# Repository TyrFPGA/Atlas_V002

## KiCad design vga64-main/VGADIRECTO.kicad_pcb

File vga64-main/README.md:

# vga64
Adaptador directo de hdmi a vga para la atlasfpga. Diseño usando Kicad 6.0

La profundidad actual que conseguimos de 64 colores usando 2 bits por color, por eso la llamamos vga64 aunque también podría llamarse vga222.

El adaptador puede ser usado solo o con una adaptador vga<->scart si el core lo permite sin problemas.

# Esquemas
[https://github.com/AtlasFPGA/vga64/blob/main/VGADIRECTO.pdf]

# Material
* 1 x PCB vga
* 1 x conector HDMI 
* 1 x conector VGA
* 1 x resistencia 1206 -  1k ohm
* 3 x resistencia 1206 - 820 ohm 
* 3 x resistencia 1206 - 240 ohm

# URL compras
* 1 x PCB lo hicimos en la página https://jlcpcb.com/ usando los gerbers: https://github.com/AtlasFPGA/vga64/raw/main/gerbers_vga64_atlas_1206.zip
* 1 x HDMI modelo 10029449-111RLF -> https://es.farnell.com/amphenol-icc-fci/10029449-111rlf/conector-hdmi-19-pos-hembra-smt/dp/2751197
* 1 x Conector VGA -> https://es.rs-online.com/web/p/conectores-d-sub/6740971
* 1 x resistencia 1206 -  1k ohm -> https://es.farnell.com/multicomp-pro/mp003719/res-1k-1-0-25w-1206-pel-c-gruesa/dp/3392916
* 3 x resistencia 1206 - 820 ohm -> https://es.farnell.com/multicomp-pro/mp003717/res-820r-1-0-25w-1206-pel-c-gruesa/dp/3392914
* 3 x resistencia 1206 - 240 ohm -> https://es.farnell.com/multicomp-pro/mp003703/res-240r-1-0-25w-1206-pel-c-gruesa/dp/3392898

# Equivalencias de pineado para cambiar en Quartus
```
## HDMI Direct ATLAS_V002_CYC1000                                         ### VGA222 adaptador de 64Colores
set_location_assignment PIN_L16 -to TMDS[0] # CLK-                        ### HS
set_location_assignment PIN_L15 -to TMDS[1] # CLK+ # clock channel        ### VS
set_location_assignment PIN_P1 -to TMDS[2]  # 0-                          ### BLUE[0]
set_location_assignment PIN_P2 -to TMDS[3]  # 0+   # blue channel         ### BLUE[1]
set_location_assignment PIN_J1 -to TMDS[4]  # 1-                          ### GREEN[0]
set_location_assignment PIN_J2 -to TMDS[5]  # 1+   # green channel        ### GREEN[1]
set_location_assignment PIN_N1 -to TMDS[6]  # 2-                          ### RED[0]
set_location_assignment PIN_N2 -to TMDS[7]  # 2+   # red channel          ### RED[1]
```

Proyecto original de @subcriticalia y @Nabateo.

Gracias a @Rhoderik por el convertir el proyecto a smd 1206 y a @Somhi (@somhic) por la ayuda / revisión como siempre.

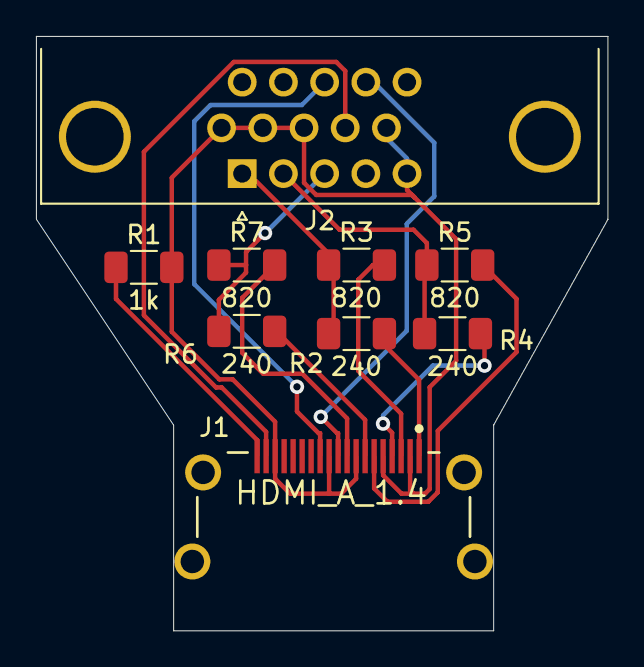
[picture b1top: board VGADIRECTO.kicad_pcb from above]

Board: 2 copper layers, 31.8 x 33.0 mm, 9 parts (0 on the bottom side), 14 nets.

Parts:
J1: HDMI_A_1.4; Amphenol_ICC-10029449-111RLF-MFG
J2: DB15_Female_HighDensity; DSUB-15-HD_Female_Horizontal_P2.29x2.54mm_EdgePinOffset3.03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
R1: 1k; R_1206_3216Metric_Pad1.30x1.75mm_HandSolder
R2, R4, R6: 240; R_1206_3216Metric_Pad1.30x1.75mm_HandSolder
R3, R5, R7: 820; R_1206_3216Metric_Pad1.30x1.75mm_HandSolder

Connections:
+5V: J1.18 (+5V), J2.9
GND: J1.2 (D2S), J1.5 (D1S), J1.8 (D0S), J1.11 (CKS), J1.17 (GND), J2.5, J2.6, J2.7, J2.8, J2.10, R1.2
unnamed: J1.19 (HPD/HEAC-), R1.1
VGA222_B0: J1.9 (D0-), R7.2
VGA222_B1: J1.7 (D0+), R6.2
VGA222_G0: J1.6 (D1-), R5.2
VGA222_G1: J1.4 (D1+), R4.2
VGA222_HS: J1.12 (CK-), J2.13
VGA222_R0: J1.3 (D2-), R3.2
VGA222_R1: J1.1 (D2+), R2.2
VGA222_VS: J1.10 (CK+), J2.14
VGAB: J2.3, R6.1, R7.1
VGAG: J2.2, R4.1, R5.1
VGAR: J2.1, R2.1, R3.1

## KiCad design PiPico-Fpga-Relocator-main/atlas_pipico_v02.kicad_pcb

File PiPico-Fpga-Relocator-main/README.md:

# PiPico-Fpga-Relocator
PCB for plug a PiPico on MKR bus for use Atlas resources

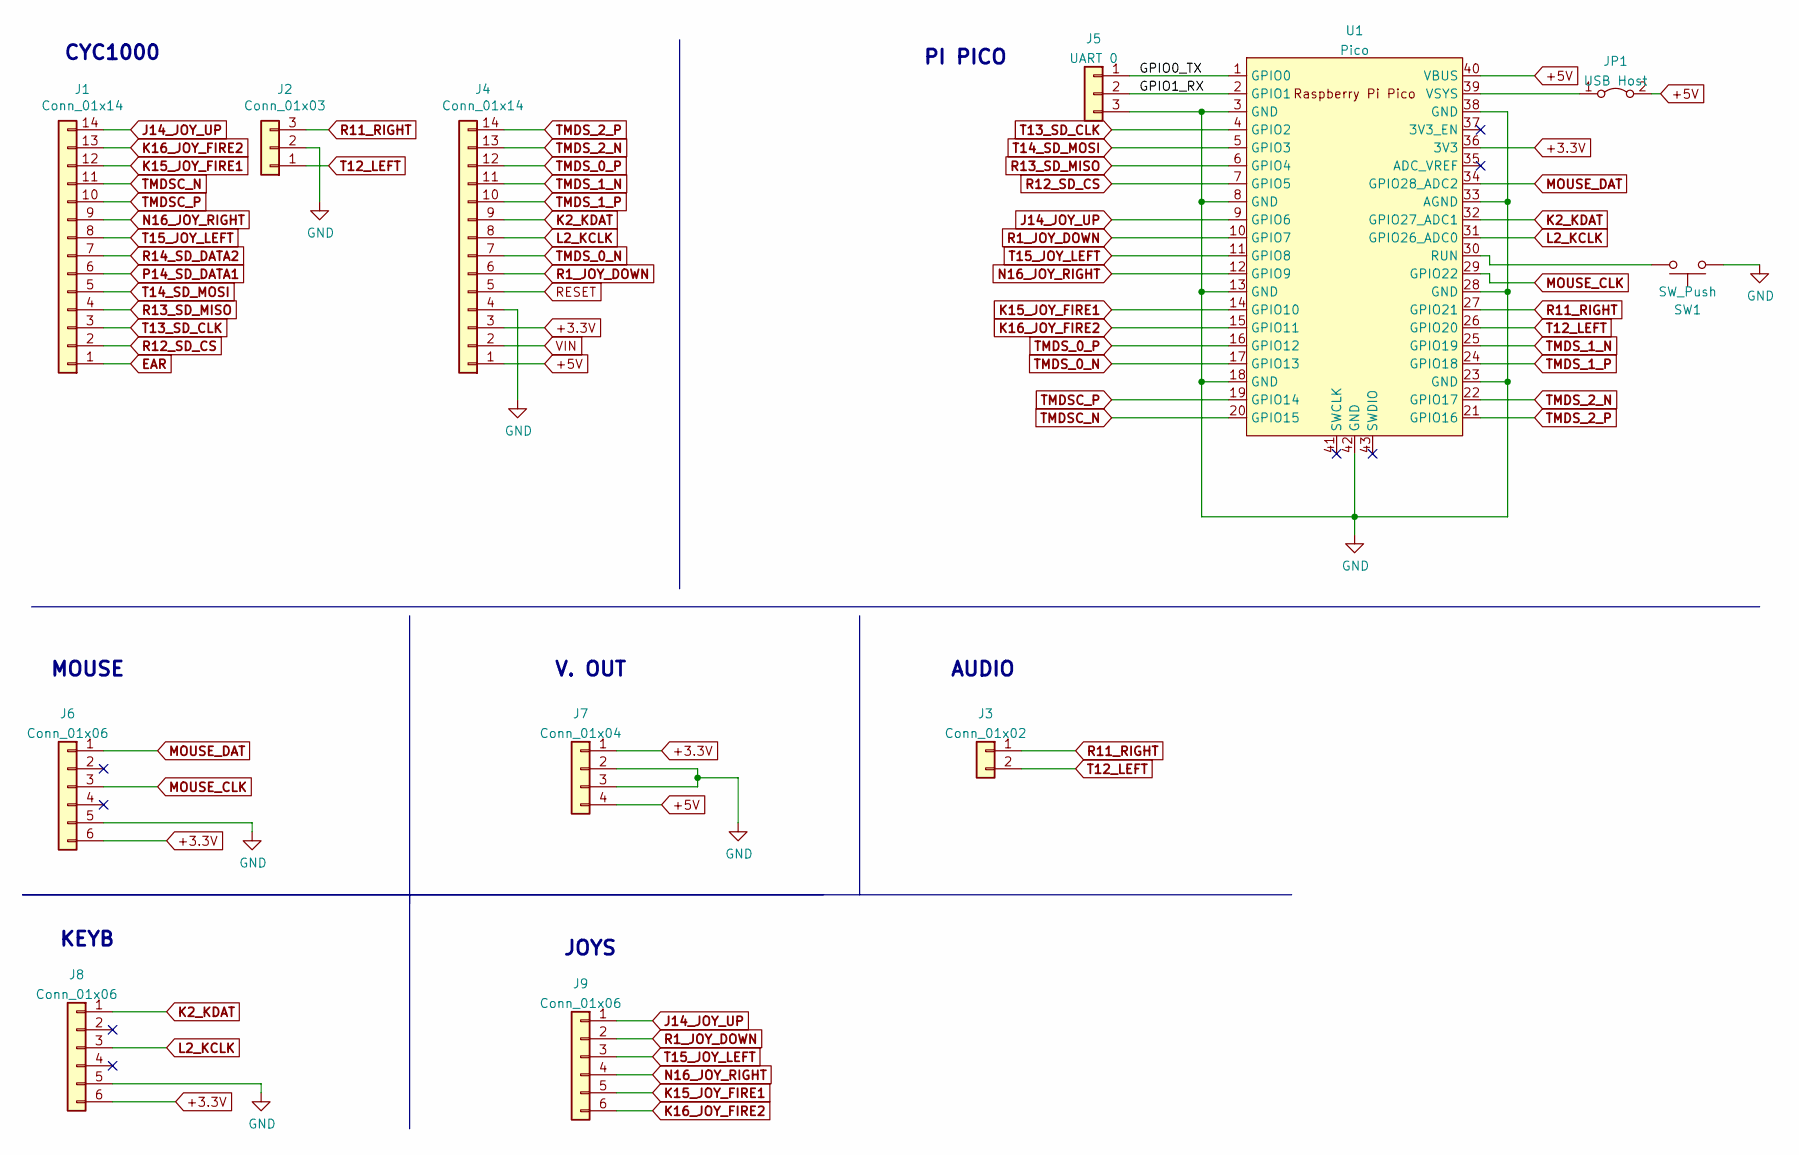
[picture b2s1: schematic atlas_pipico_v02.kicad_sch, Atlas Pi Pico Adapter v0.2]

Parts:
J1, J4: Conn_01x14; PinHeader_1x14_P2.54mm_Vertical
J2: Conn_01x03; PinHeader_1x03_P2.54mm_Vertical
J3: Conn_01x02; PinHeader_1x02_P2.54mm_Vertical
J5: UART 0; PinHeader_1x03_P2.54mm_Vertical
J6, J8, J9: Conn_01x06; PinHeader_1x06_P2.54mm_Vertical
J7: Conn_01x04; PinHeader_1x04_P2.54mm_Vertical
JP1: USB Host; PinHeader_1x02_P2.54mm_Vertical
SW1: SW_Push; SW_PUSH_6mm
U1: Pico; RPi_Pico_SMD_TH

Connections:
+3.3V: J4.3, J6.6, J7.1, J8.6, U1.36 (3V3)
+5V: J4.1, J7.4, JP1.2 (B), U1.40 (VBUS)
/GPIO0_TX: J5.1, U1.1 (GPIO0)
/GPIO1_RX: J5.2, U1.2 (GPIO1)
EAR: J1.1
GND: J2.2, J4.4, J5.3, J6.5, J7.2, J7.3, J8.5, SW1.2, U1.3 (GND), U1.8 (GND), U1.13 (GND), U1.18 (GND), U1.23 (GND), U1.28 (GND), U1.33 (AGND), U1.38 (GND), U1.42 (GND)
J14_JOY_UP: J1.14, J9.1, U1.9 (GPIO6)
K2_KDAT: J4.9, J8.1, U1.32 (GPIO27_ADC1)
K15_JOY_FIRE1: J1.12, J9.5, U1.14 (GPIO10)
K16_JOY_FIRE2: J1.13, J9.6, U1.15 (GPIO11)
L2_KCLK: J4.8, J8.3, U1.31 (GPIO26_ADC0)
MOUSE_CLK: J6.3, U1.29 (GPIO22)
MOUSE_DAT: J6.1, U1.34 (GPIO28_ADC2)
N16_JOY_RIGHT: J1.9, J9.4, U1.12 (GPIO9)
unnamed: JP1.1 (A), U1.39 (VSYS)
unnamed: SW1.1, U1.30 (RUN)
P14_SD_DATA1: J1.6
R1_JOY_DOWN: J4.6, J9.2, U1.10 (GPIO7)
R11_RIGHT: J2.3, J3.1, U1.27 (GPIO21)
R12_SD_CS: J1.2, U1.7 (GPIO5)
R13_SD_MISO: J1.4, U1.6 (GPIO4)
R14_SD_DATA2: J1.7
RESET: J4.5
T12_LEFT: J2.1, J3.2, U1.26 (GPIO20)
T13_SD_CLK: J1.3, U1.4 (GPIO2)
T14_SD_MOSI: J1.5, U1.5 (GPIO3)
T15_JOY_LEFT: J1.8, J9.3, U1.11 (GPIO8)
TMDSC_N: J1.11, U1.20 (GPIO15)
TMDSC_P: J1.10, U1.19 (GPIO14)
TMDS_0_N: J4.7, U1.17 (GPIO13)
TMDS_0_P: J4.12, U1.16 (GPIO12)
TMDS_1_N: J4.11, U1.25 (GPIO19)
TMDS_1_P: J4.10, U1.24 (GPIO18)
TMDS_2_N: J4.13, U1.22 (GPIO17)
TMDS_2_P: J4.14, U1.21 (GPIO16)
VIN: J4.2

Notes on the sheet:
MOUSE
CYC1000
AUDIO
KEYB
JOYS
PI PICO
V. OUT

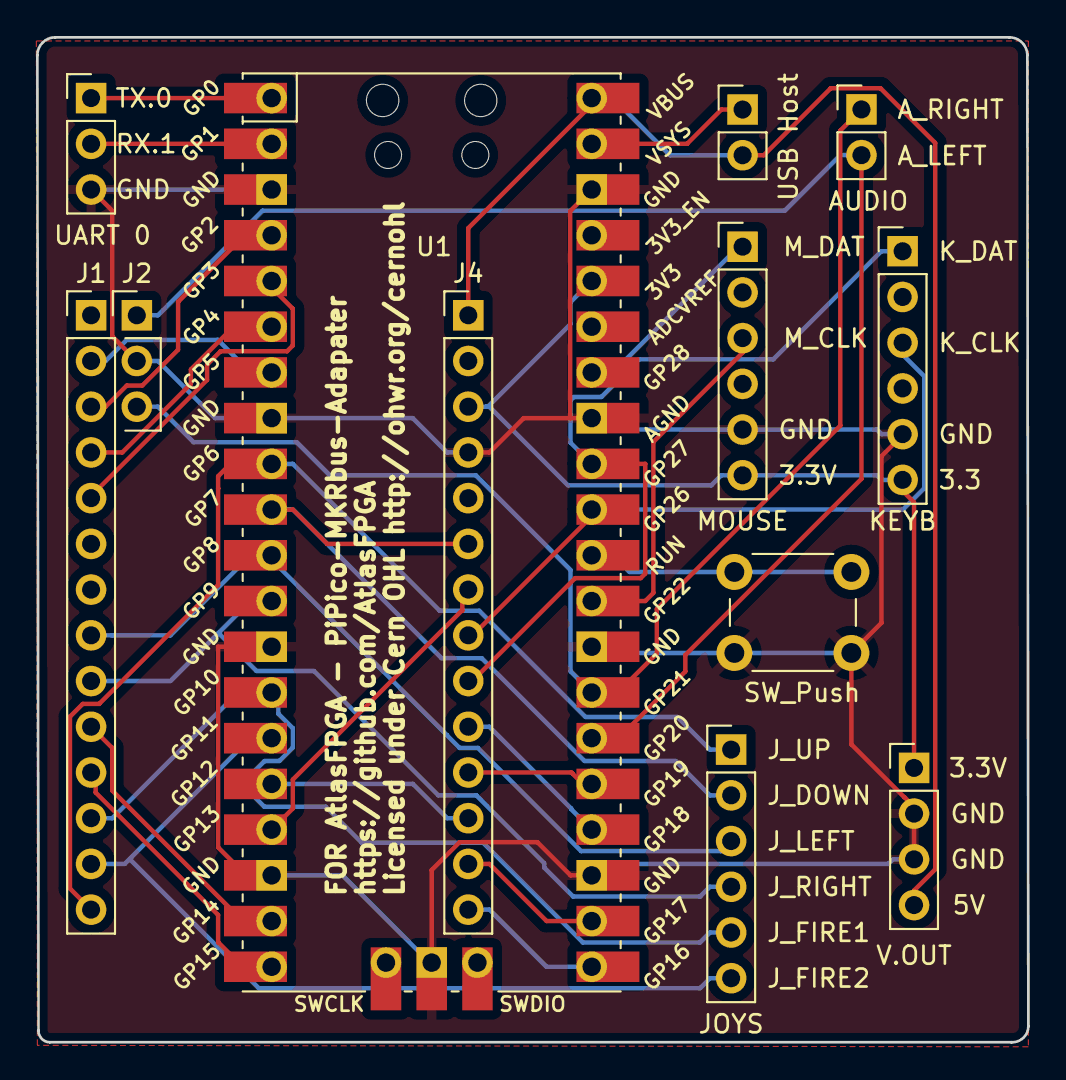
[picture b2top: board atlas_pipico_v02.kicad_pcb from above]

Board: 2 copper layers, 55.1 x 55.8 mm, 12 parts (0 on the bottom side), 31 nets.

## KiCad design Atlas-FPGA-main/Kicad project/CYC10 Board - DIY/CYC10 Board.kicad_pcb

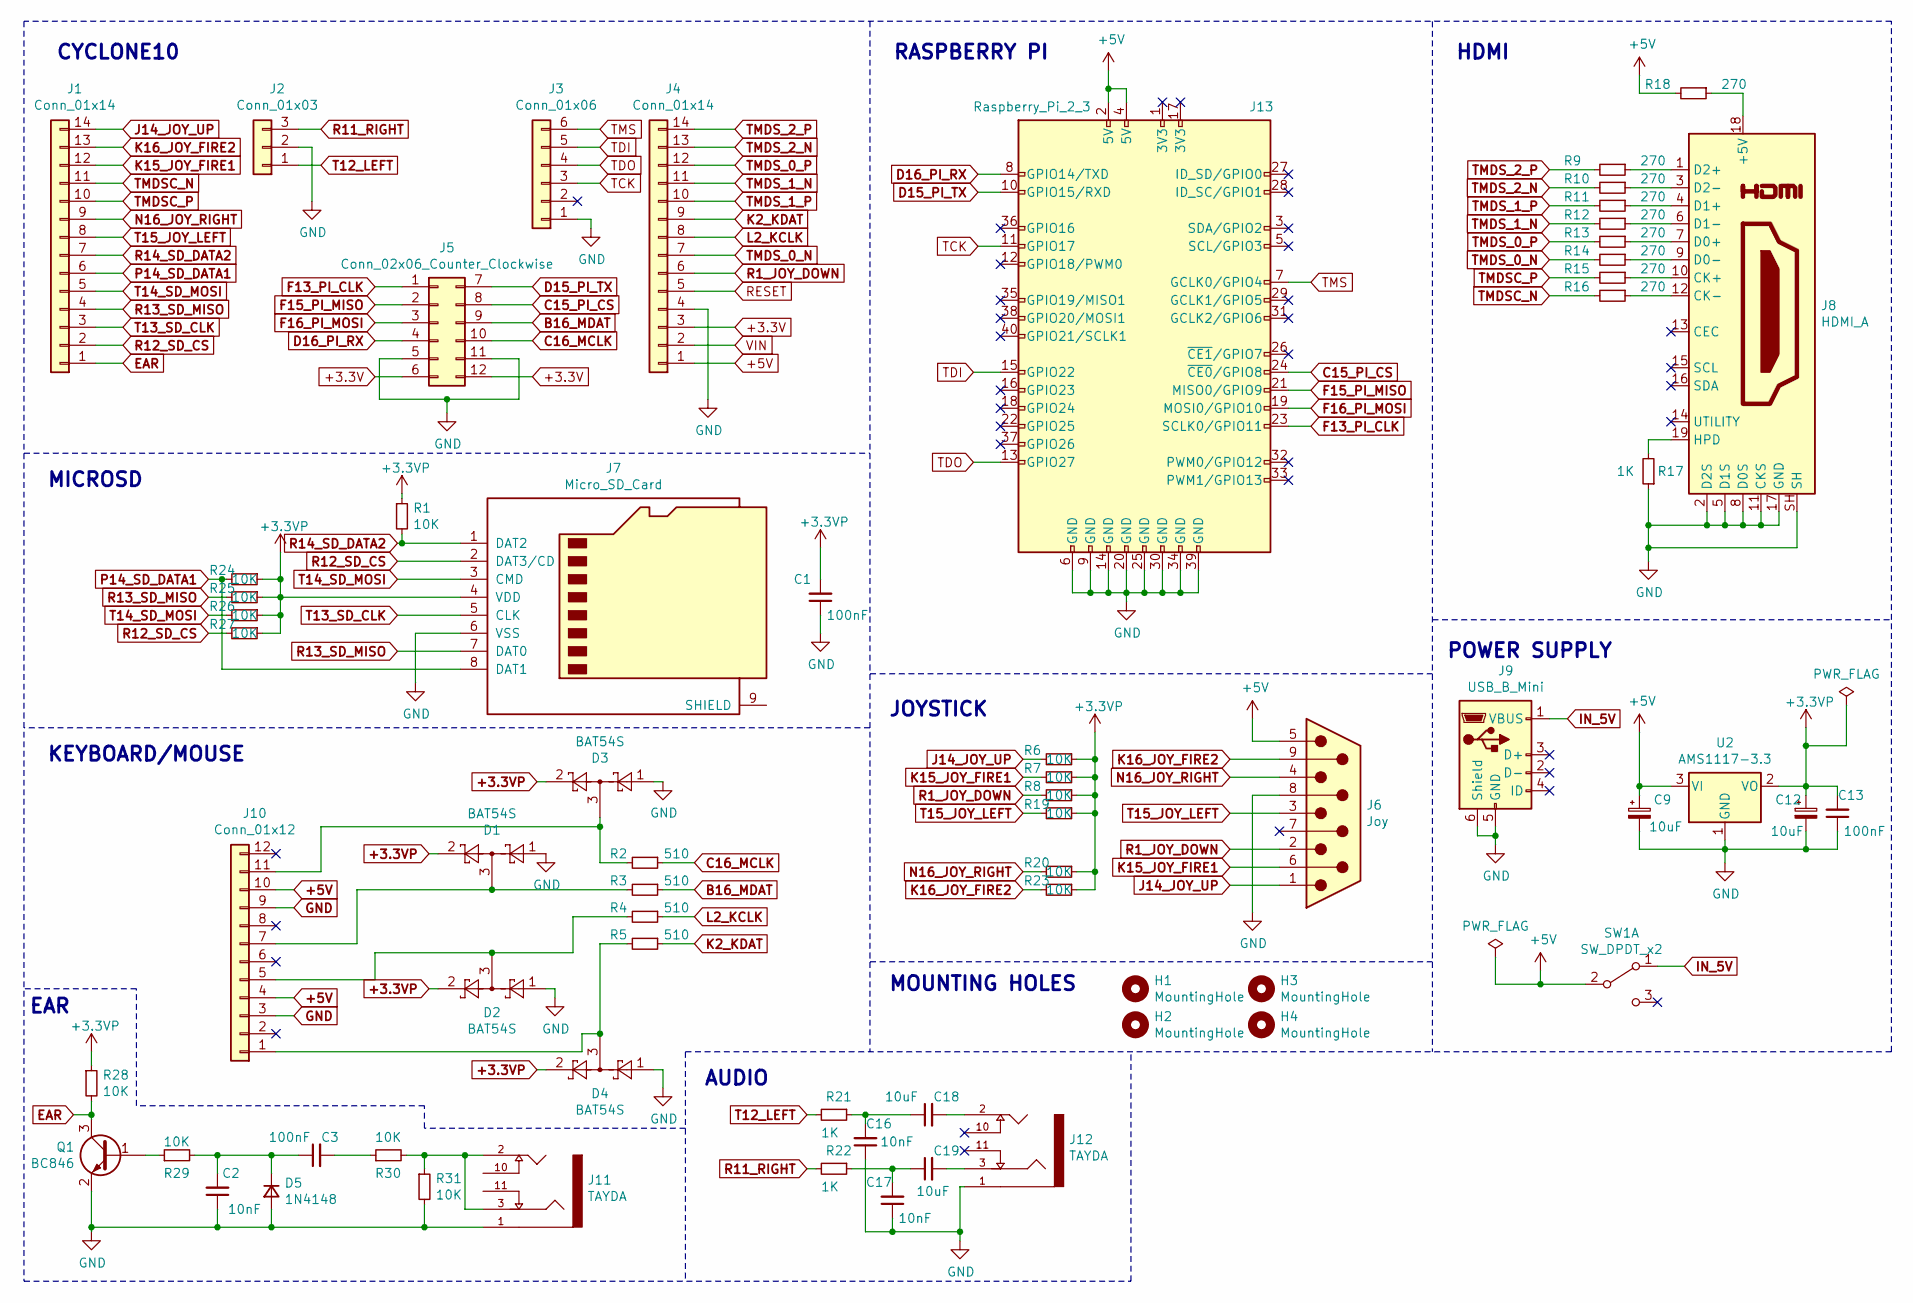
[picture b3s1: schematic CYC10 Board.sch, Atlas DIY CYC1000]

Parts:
C1, C3, C13: 100nF; C_0805_2012Metric
C2, C16, C17: 10nF; C_0805_2012Metric
C9, C12, C18, C19: 10uF; C_0805_2012Metric
D1, D2, D3, D4: BAT54S; SOT-23
D5: 1N4148; D_MiniMELF
H1, H2, H3, H4: MountingHole; MountingHole_3.2mm_M3
J1, J4: Conn_01x14; PinHeader_1x14_P2.54mm_Vertical
J2: Conn_01x03; PinHeader_1x03_P2.54mm_Vertical
J3: Conn_01x06; PinHeader_1x06_P2.54mm_Vertical
J5: Conn_02x06_Counter_Clockwise; PMOD
J6: Joy; DSUB-9_Male_Horizontal_P2.77x2.84mm_EdgePinOffset9.90mm_Hou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
J7: Micro_SD_Card; Conn_uSDcard1
J8: HDMI_A; HDMI_BIEN
J9: USB_B_Mini; USB_Mini-B_Wuerth_65100516121_Horizontal
J10: Conn_01x12; PS2_DOBLE
J11, J12: TAYDA; Tayda_Audio_Bien
J13: Raspberry_Pi_2_3; Conector_PI
Q1: BC846; SOT-23
R1, R6, R7, R8, R19, R20, R23, R24, R25, R26, R27, R28, R29, R30, R31: 10K; R_0805_2012Metric
R2, R3, R4, R5: 510; R_0805_2012Metric
R9, R10, R11, R12, R13, R14, R15, R16, R18: 270; R_0805_2012Metric
R17, R21, R22: 1K; R_0805_2012Metric
SW1: SW_DPDT_x2; Switch
U2: AMS1117-3.3; SOT-223-3_TabPin2

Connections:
+3.3V: J4.3, J5.6, J5.12
+3.3VP: C1.2, C12.1, C13.2, D1.2, D2.2, D3.2, D4.2, J7.4 (VDD), R1.1, R6.1, R7.1, R8.1, R19.1, R20.1, R23.1, R24.1, R25.1, R26.1, R27.1, R28.1, U2.2 (VO)
+5V: C9.1, J4.1, J6.5, J10.4, J10.10, J13.2 (5V), J13.4 (5V), R18.2, SW1.2 (B), U2.3 (VI)
B16_MDAT: J5.9, R3.1
C15_PI_CS: J5.8, J13.24 (~CE0~/GPIO8)
C16_MCLK: J5.10, R2.1
D15_PI_TX: J5.7, J13.10 (GPIO15/RXD)
D16_PI_RX: J5.4, J13.8 (GPIO14/TXD)
EAR: J1.1, Q1.3 (C), R28.2
F13_PI_CLK: J5.1, J13.23 (SCLK0/GPIO11)
F15_PI_MISO: J5.2, J13.21 (MISO0/GPIO9)
F16_PI_MOSI: J5.3, J13.19 (MOSI0/GPIO10)
GND: C1.1, C2.1, C9.2, C12.2, C13.1, C16.1, C17.1, D1.1, D2.1, D3.1, D4.1, D5.2 (A), J2.2, J3.1, J4.4, J5.5, J5.11, J6.8, J7.6 (VSS), J8.2 (D2S), J8.5 (D1S), J8.8 (D0S), J8.11 (CKS), J8.17 (GND), J8.SH, J9.5 (GND), J9.6 (Shield), J10.3, J10.9, J11.1, J12.1, J13.6 (GND), J13.9 (GND), J13.14 (GND), J13.20 (GND), J13.25 (GND), J13.30 (GND), J13.34 (GND), J13.39 (GND), Q1.2 (E), R17.1, R31.2, U2.1 (GND)
IN_5V: J9.1 (VBUS), SW1.1 (A)
J14_JOY_UP: J1.14, J6.1, R6.2
K2_KDAT: J4.9, R5.1
K15_JOY_FIRE1: J1.12, J6.6, R7.2
K16_JOY_FIRE2: J1.13, J6.9, R23.2
L2_KCLK: J4.8, R4.1
N16_JOY_RIGHT: J1.9, J6.4, R20.2
unnamed: C2.2, C3.1, D5.1 (K), R29.2
unnamed: C3.2, R30.1
unnamed: C16.2, C18.1, R21.1
unnamed: C17.2, C19.1, R22.1
unnamed: C18.2, J12.2
unnamed: C19.2, J12.3
unnamed: D1.3, J10.7, R3.2
unnamed: D2.3, J10.5, R4.2
unnamed: D3.3, J10.11, R2.2
unnamed: D4.3, J10.1, R5.2
unnamed: J8.1 (D2+), R9.1
unnamed: J8.3 (D2-), R10.1
unnamed: J8.4 (D1+), R11.1
unnamed: J8.6 (D1-), R12.1
unnamed: J8.7 (D0+), R13.1
unnamed: J8.9 (D0-), R14.1
unnamed: J8.10 (CK+), R15.1
unnamed: J8.12 (CK-), R16.1
unnamed: J8.18 (+5V), R18.1
unnamed: J8.19 (HPD), R17.2
unnamed: J11.2, J11.3, R30.2, R31.1
unnamed: Q1.1 (B), R29.1
P14_SD_DATA1: J1.6, J7.8 (DAT1), R24.2
R1_JOY_DOWN: J4.6, J6.2, R8.2
R11_RIGHT: J2.3, R22.2
R12_SD_CS: J1.2, J7.2 (DAT3/CD), R27.2
R13_SD_MISO: J1.4, J7.7 (DAT0), R25.2
R14_SD_DATA2: J1.7, J7.1 (DAT2), R1.2
RESET: J4.5
T12_LEFT: J2.1, R21.2
T13_SD_CLK: J1.3, J7.5 (CLK)
T14_SD_MOSI: J1.5, J7.3 (CMD), R26.2
T15_JOY_LEFT: J1.8, J6.3, R19.2
TCK: J3.3, J13.11 (GPIO17)
TDI: J3.5, J13.15 (GPIO22)
TDO: J3.4, J13.13 (GPIO27)
TMDSC_N: J1.11, R16.2
TMDSC_P: J1.10, R15.2
TMDS_0_N: J4.7, R14.2
TMDS_0_P: J4.12, R13.2
TMDS_1_N: J4.11, R12.2
TMDS_1_P: J4.10, R11.2
TMDS_2_N: J4.13, R10.2
TMDS_2_P: J4.14, R9.2
TMS: J3.6, J13.7 (GCLK0/GPIO4)
VIN: J4.2

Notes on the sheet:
JOYSTICK
POWER SUPPLY
AUDIO
KEYBOARD/MOUSE
MICROSD
CYCLONE10
RASPBERRY PI
HDMI
MOUNTING HOLES
EAR

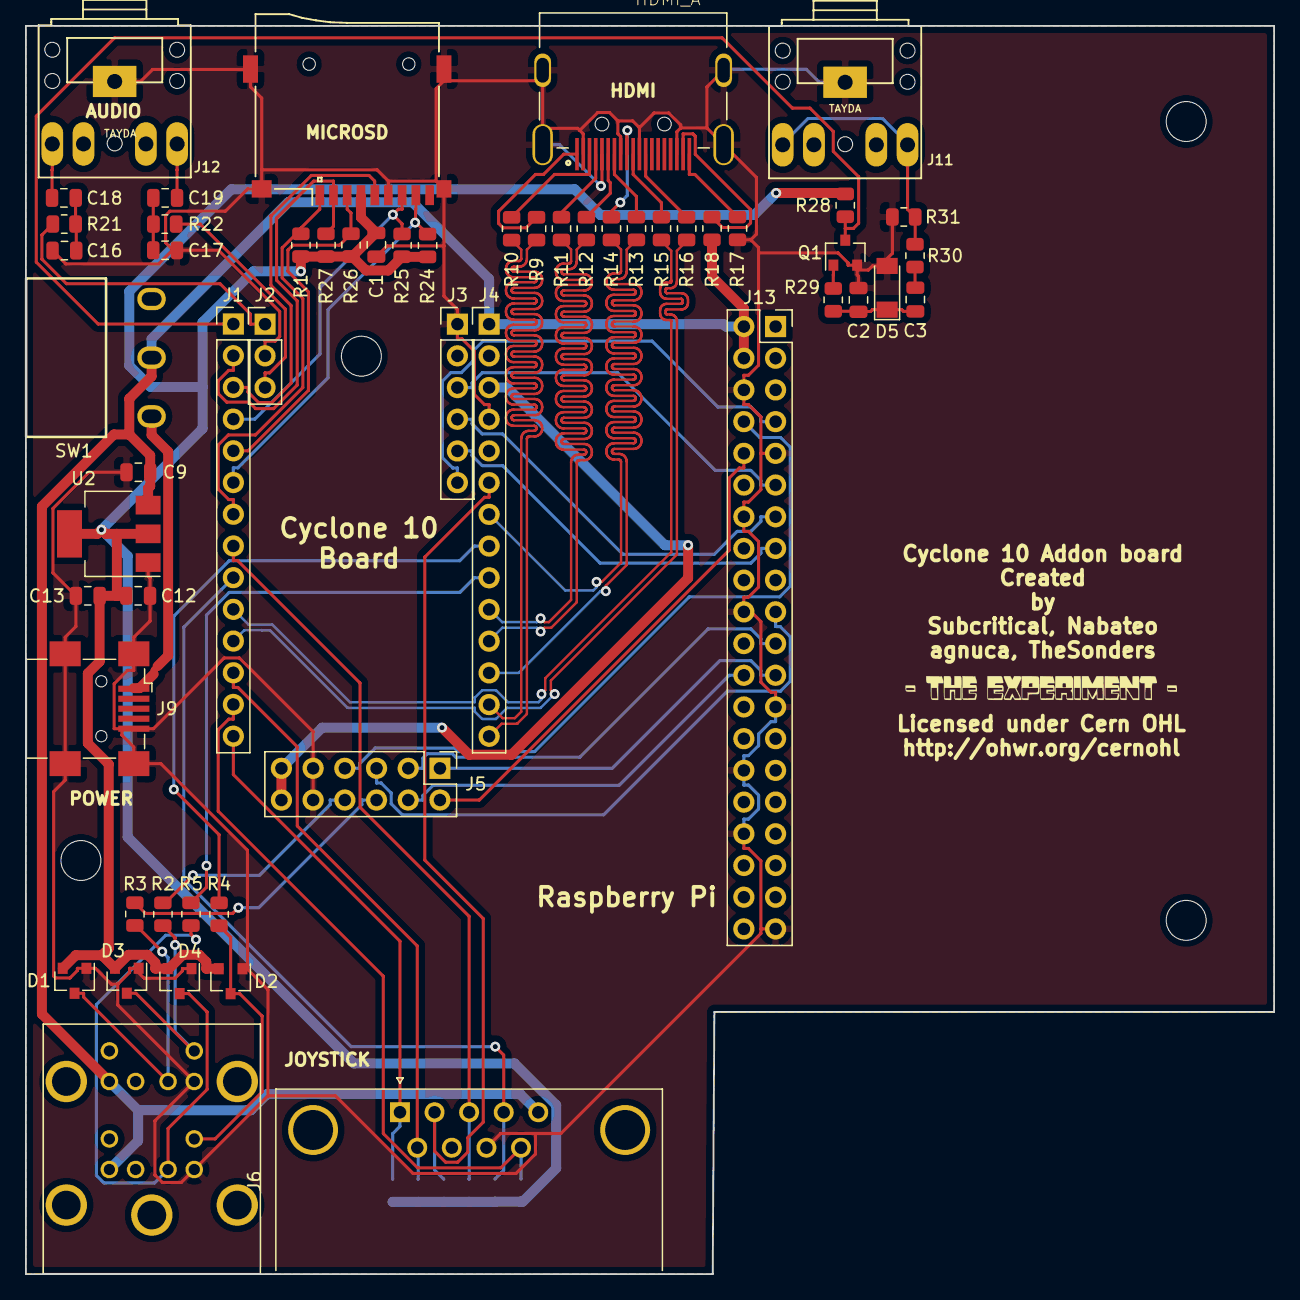
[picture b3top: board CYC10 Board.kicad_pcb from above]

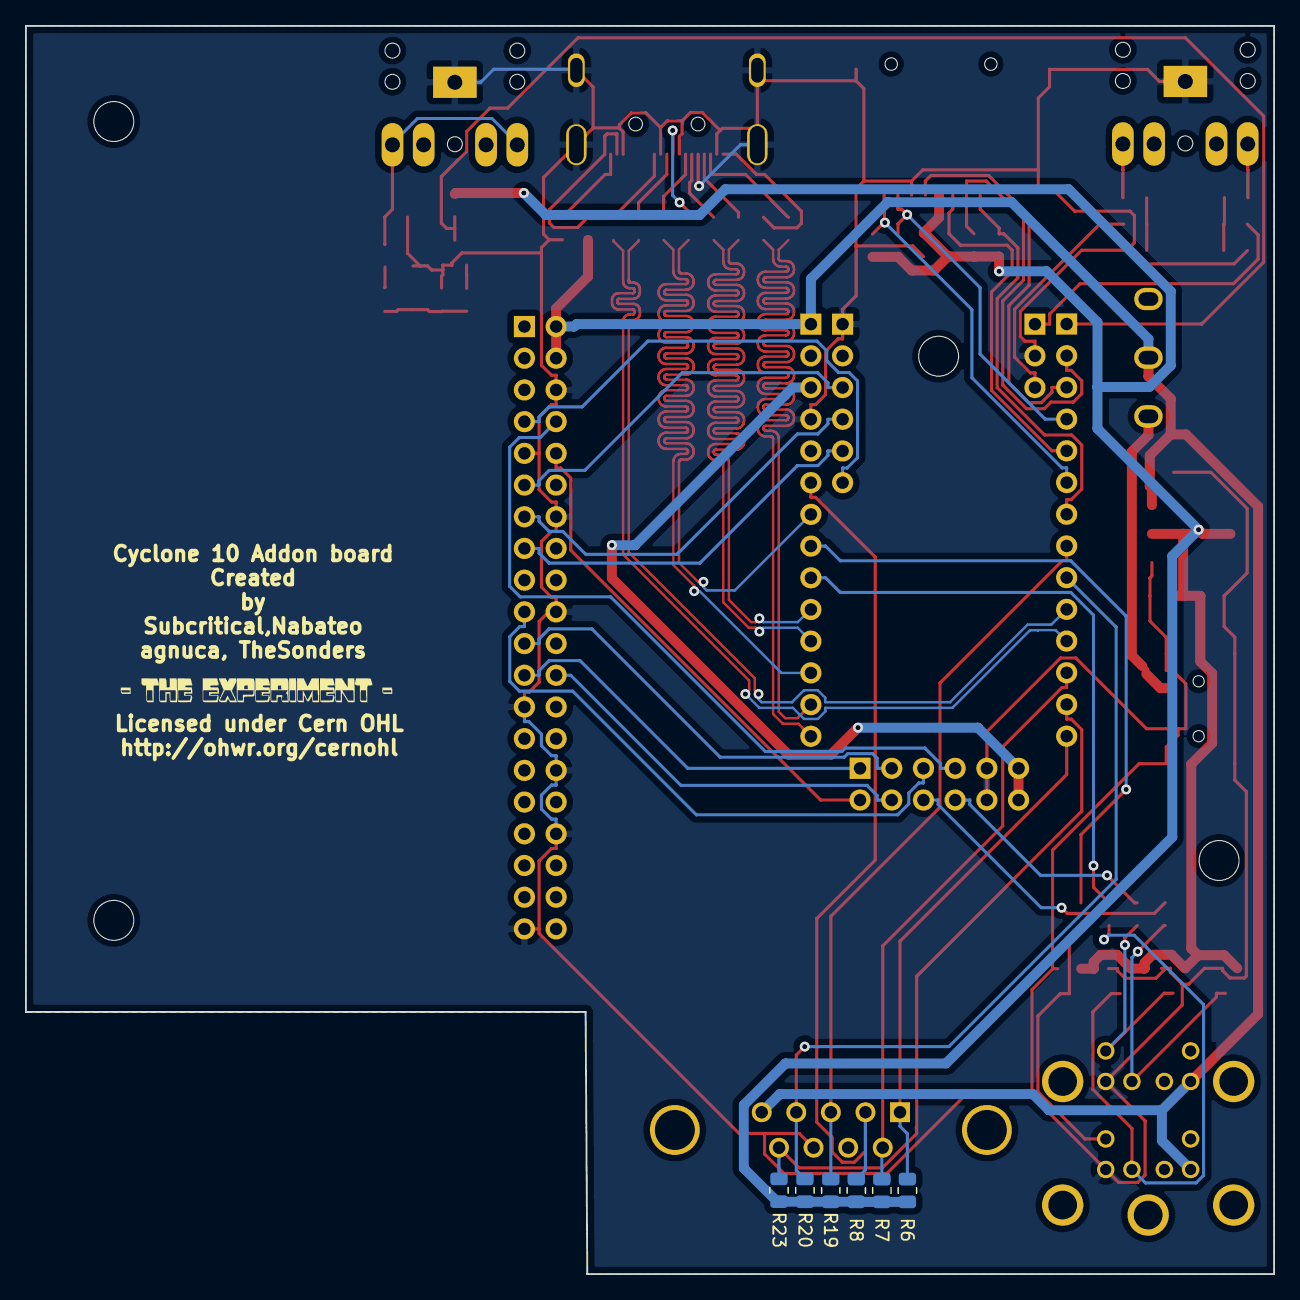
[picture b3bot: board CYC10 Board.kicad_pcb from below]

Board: 2 copper layers, 100.0 x 100.0 mm, 66 parts (6 on the bottom side), 64 nets.

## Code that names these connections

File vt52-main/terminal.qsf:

# -------------------------------------------------------------------------- #
#
# Copyright (C) 2018  Intel Corporation. All rights reserved.
# Your use of Intel Corporation's design tools, logic functions 
# and other software and tools, and its AMPP partner logic 
# functions, and any output files from any of the foregoing 
# (including device programming or simulation files), and any 
# associated documentation or information are expressly subject 
# to the terms and conditions of the Intel Program License 
# Subscription Agreement, the Intel Quartus Prime License Agreement,
# the Intel FPGA IP License Agreement, or other applicable license
# agreement, including, without limitation, that your use is for
# the sole purpose of programming logic devices manufactured by
# Intel and sold by Intel or its authorized distributors.  Please
# refer to the applicable agreement for further details.
#
# -------------------------------------------------------------------------- #
#
# Quartus Prime
# Version 18.0.0 Build 614 04/24/2018 SJ Standard Edition
# Date created = 08:58:44  November 04, 2020
#
# -------------------------------------------------------------------------- #
#
# Notes:
#
# 1) The default values for assignments are stored in the file:
#		terminal_assignment_defaults.qdf
#    If this file doesn't exist, see file:
#		assignment_defaults.qdf
#
# 2) Altera recommends that you do not modify this file. This
#    file is updated automatically by the Quartus Prime software
#    and any changes you make may be lost or overwritten.
#
# -------------------------------------------------------------------------- #


set_global_assignment -name FAMILY "Cyclone 10 LP"
set_global_assignment -name DEVICE 10CL025YU256C8G
set_global_assignment -name TOP_LEVEL_ENTITY terminal
set_global_assignment -name ORIGINAL_QUARTUS_VERSION 18.0.0
set_global_assignment -name PROJECT_CREATION_TIME_DATE "08:58:44  NOVEMBER 04, 2020"
set_global_assignment -name LAST_QUARTUS_VERSION "17.1.0 Lite Edition"
set_global_assignment -name PROJECT_OUTPUT_DIRECTORY output_files

set_global_assignment -name MIN_CORE_JUNCTION_TEMP 0
set_global_assignment -name MAX_CORE_JUNCTION_TEMP 85
set_global_assignment -name ERROR_CHECK_FREQUENCY_DIVISOR 1
set_global_assignment -name ENABLE_OCT_DONE OFF
set_global_assignment -name ENABLE_CONFIGURATION_PINS OFF
set_global_assignment -name ENABLE_BOOT_SEL_PIN OFF
set_global_assignment -name USE_CONFIGURATION_DEVICE OFF
set_global_assignment -name CRC_ERROR_OPEN_DRAIN OFF

set_global_assignment -name STRATIX_DEVICE_IO_STANDARD "3.3-V LVTTL"
set_global_assignment -name CYCLONEII_RESERVE_NCEO_AFTER_CONFIGURATION "USE AS REGULAR IO"
set_global_assignment -name OUTPUT_IO_TIMING_NEAR_END_VMEAS "HALF VCCIO" -rise
set_global_assignment -name OUTPUT_IO_TIMING_NEAR_END_VMEAS "HALF VCCIO" -fall
set_global_assignment -name OUTPUT_IO_TIMING_FAR_END_VMEAS "HALF SIGNAL SWING" -rise
set_global_assignment -name OUTPUT_IO_TIMING_FAR_END_VMEAS "HALF SIGNAL SWING" -fall
set_global_assignment -name POWER_PRESET_COOLING_SOLUTION "23 MM HEAT SINK WITH 200 LFPM AIRFLOW"
set_global_assignment -name POWER_BOARD_THERMAL_MODEL "NONE (CONSERVATIVE)"
set_global_assignment -name SMART_RECOMPILE ON
set_global_assignment -name STRATIXV_CONFIGURATION_SCHEME "PASSIVE SERIAL"
set_global_assignment -name CYCLONEIII_CONFIGURATION_DEVICE EPCQ16
set_global_assignment -name NUM_PARALLEL_PROCESSORS ALL

set_global_assignment -name GENERATE_RBF_FILE ON
set_global_assignment -name GENERATE_SVF_FILE ON
set_global_assignment -name ON_CHIP_BITSTREAM_DECOMPRESSION OFF

set_global_assignment -name RESERVE_ALL_UNUSED_PINS_WEAK_PULLUP "AS INPUT TRI-STATED"

set_global_assignment -name EDA_SIMULATION_TOOL "ModelSim-Altera (Verilog)"
set_global_assignment -name EDA_TIME_SCALE "1 ps" -section_id eda_simulation
set_global_assignment -name EDA_OUTPUT_DATA_FORMAT "VERILOG HDL" -section_id eda_simulation

#======================

set_location_assignment PIN_M2 -to clk12

set_location_assignment PIN_N6 -to resetbtn

#set_location_assignment PIN_L16 -to vgah
#set_location_assignment PIN_L15 -to vgav
#set_location_assignment PIN_P1 -to vgab[0]
#set_location_assignment PIN_P2 -to vgab[1]
#set_location_assignment PIN_J1 -to vgag[0]
#set_location_assignment PIN_J2 -to vgag[1]
#set_location_assignment PIN_N1 -to vgar[0]
#set_location_assignment PIN_N2 -to vgar[1]

set_location_assignment PIN_L16 -to TMDS[0]
  # CLK-                        ### VGA_HS
set_location_assignment PIN_L15 -to TMDS[1]
  # CLK+ # clock channel        ### VGA_VS
set_location_assignment PIN_P1 -to TMDS[2]
  # 0-                          ### VGA_B[0]
set_location_assignment PIN_P2 -to TMDS[3]
 # 0+   # blue channel         ### VGA_B[1]
set_location_assignment PIN_J1 -to TMDS[4]
  # 1-                          ### VGA_G[0]
set_location_assignment PIN_J2 -to TMDS[5]
  # 1+   # green channel        ### VGA_G[1]
set_location_assignment PIN_N1 -to TMDS[6]
  # 2-                          ### VGA_R[0]
set_location_assignment PIN_N2 -to TMDS[7]
  # 2+   # red channel          ### VGA_R[1]

set_location_assignment PIN_L2 -to ps2_clk
set_location_assignment PIN_K2 -to ps2_data

set_location_assignment PIN_T12 -to buzzer

set_location_assignment PIN_D16 -to uart_rx
set_location_assignment PIN_D15 -to uart_tx

#======================

set_global_assignment -name VERILOG_FILE terminal.v
set_global_assignment -name SDC_FILE terminal.sdc

set_global_assignment -name VERILOG_FILE "vt52-hdl/vtvic.v"
set_global_assignment -name VERILOG_FILE "vt52-hdl/vtuart.v"
set_global_assignment -name VERILOG_FILE "vt52-hdl/vtreset.v"
set_global_assignment -name VERILOG_FILE "vt52-hdl/vtram.v"
set_global_assignment -name QIP_FILE "vt52-hdl/vtmem.qip"
set_global_assignment -name VERILOG_FILE "vt52-hdl/vt52.v"
set_global_assignment -name VERILOG_FILE "vt52-hdl/vregs.v"
set_global_assignment -name VERILOG_FILE "vt52-hdl/vm2_wb.v"
set_global_assignment -name VERILOG_FILE "vt52-hdl/vm2_plm.v"
set_global_assignment -name VERILOG_FILE "vt52-hdl/vga.v"
set_global_assignment -name VERILOG_FILE "vt52-hdl/ps2.v"
set_global_assignment -name QIP_FILE "vt52-hdl/fontrom.qip"
set_global_assignment -name QIP_FILE "vt52-hdl/pll.qip"

set_global_assignment -name QIP_FILE hdmi1/hdmi1.qip

#=======================

set_global_assignment -name PARTITION_NETLIST_TYPE SOURCE -section_id Top
set_global_assignment -name PARTITION_FITTER_PRESERVATION_LEVEL PLACEMENT_AND_ROUTING -section_id Top
set_global_assignment -name PARTITION_COLOR 16764057 -section_id Top


set_instance_assignment -name PARTITION_HIERARCHY root_partition -to | -section_id Top

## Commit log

2022-11-05 Re up

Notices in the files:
Atlas-FPGA-main/Kicad project/CYC10 Board - DIY/CYC10 Board.kicad_pcb:
Licensed under Cern OHL
PiPico-Fpga-Relocator-main/atlas_pipico_v02.kicad_pcb:
Licensed under Cern OHL http://ohwr.org/cernohl
